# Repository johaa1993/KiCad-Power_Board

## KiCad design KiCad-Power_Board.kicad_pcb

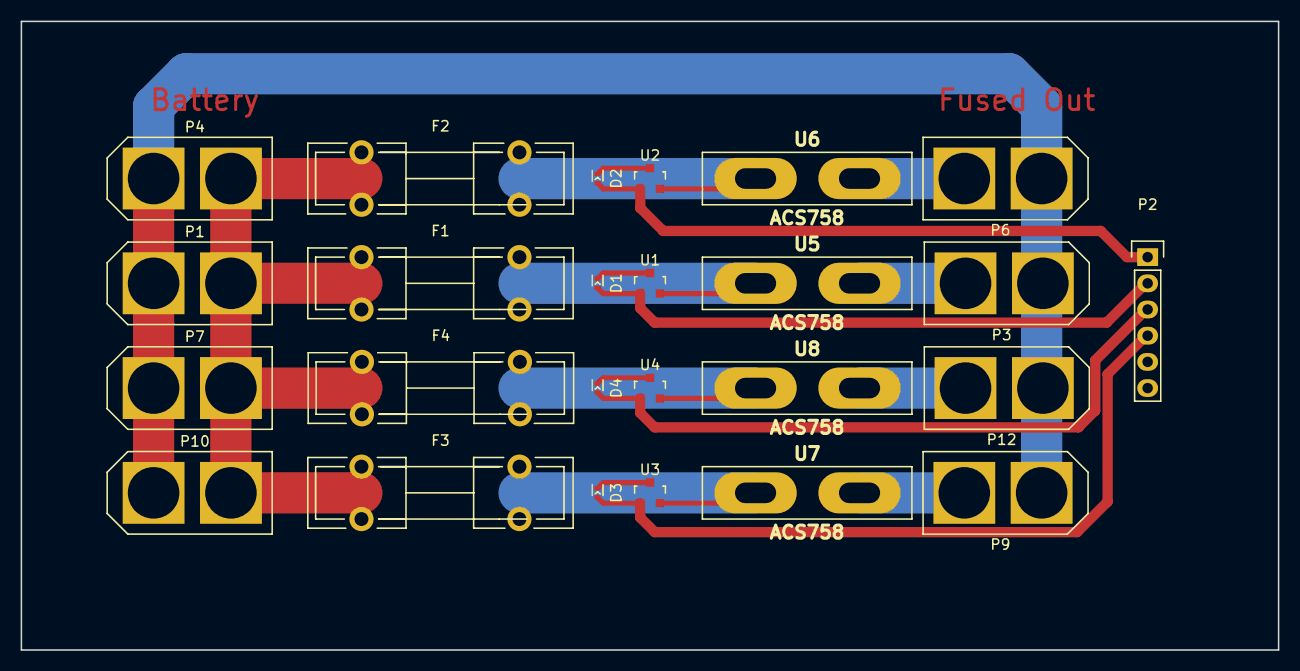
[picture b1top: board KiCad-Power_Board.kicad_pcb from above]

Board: 2 copper layers, 121.9 x 61.0 mm, 25 parts (0 on the bottom side), 14 nets.

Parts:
D1, D2, D3, D4: LED; LED_0402
F1, F2, F3, F4: FUSE; Fuseholder5x20_horiz_open_lateral_Type-II
P1, P4, P7, P10: Batt; XT60
P2: PWR_Status; Pin_Header_Straight_1x06
P3, P6, P9, P12: Out; XT60
U1, U2, U3, U4: LM3480-3.3; SOT-23
U5, U6, U7, U8: ACS758; ACS758_Vertical

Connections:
+BATT: F1.1, F2.1, F3.1, F4.1, P1.2, P4.2, P7.2, P10.2
/pwr_module1/PWR_3.3V_Status: D2.2, P2.1, U2.1
/pwr_module2/PWR_3.3V_Status: D1.2, P2.2, U1.1
/pwr_module3/PWR_3.3V_Status: D4.2, P2.3, U4.1
/pwr_module4/PWR_3.3V_Status: D3.2, P2.4, U3.1
GND: D1.1, D2.1, D3.1, D4.1, P1.1, P3.1, P4.1, P6.1, P7.1, P9.1, P10.1, P12.1, U1.3, U2.3, U3.3, U4.3
unnamed: F1.2, U1.2, U5.4
unnamed: F2.2, U2.2, U6.4
unnamed: F3.2, U3.2, U7.4
unnamed: F4.2, U4.2, U8.4
unnamed: P3.2, U5.5
unnamed: P6.2, U6.5
unnamed: P9.2, U7.5
unnamed: P12.2, U8.5

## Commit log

2016-09-24 :confetti_ball: Added .gitattributes & .gitignore files
2016-09-24 misc
2016-09-26 test
